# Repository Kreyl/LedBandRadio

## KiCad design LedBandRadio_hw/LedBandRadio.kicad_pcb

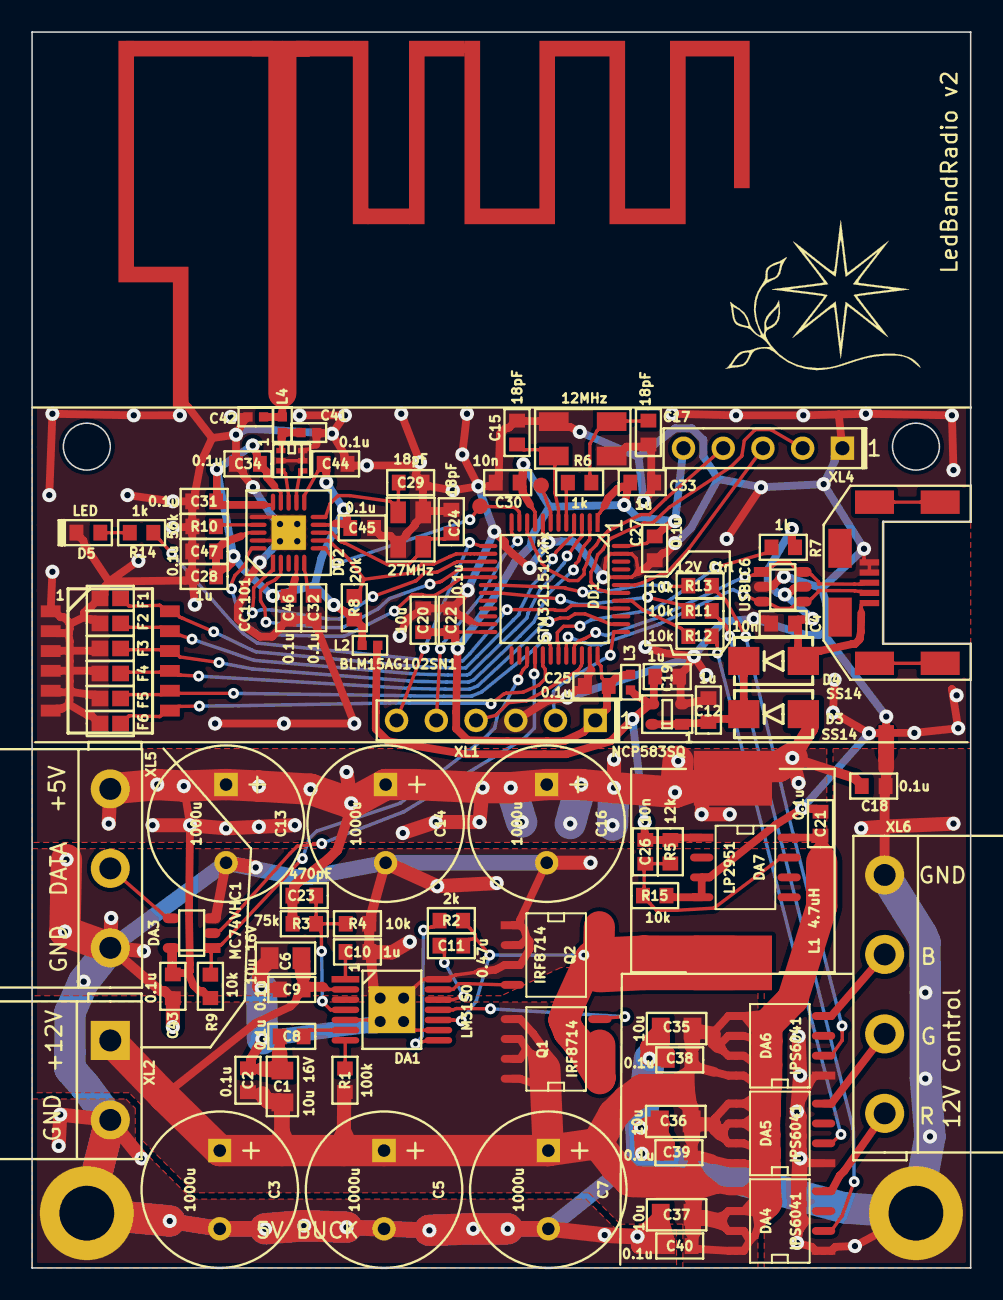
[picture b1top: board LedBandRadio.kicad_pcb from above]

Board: 2 copper layers, 60.0 x 79.0 mm, 104 parts (0 on the bottom side), 66 nets.

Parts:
ANT1: ANT_GENERAL; ANT_INVF_LEDBANDRXTX
BLN1: BALUN868JOHANSON; BALUN_JOHANSON868
C1, C6: 10u 16V; CAP_0805
C2, C8, C9, C18, C21, C22, C25, C27, C31, C32, C34, C38, C39, C40, C43, C44, C45, C46, C47: 0.1u; CAP_0603
C3, C5, C7, C13, C14, C16: 1000u; CAP_10xxR
C4, C26, C30: 10n; CAP_0603
C10, C12, C19, C28, C33: 1u; CAP_0603
C11: 0.47u; CAP_0603
C15, C17, C24, C29: 18pF; CAP_0603
C20: 10u; CAP_0603
C23: 470pF; CAP_0603
C35, C36, C37: 10u; CAP_0805
C41, C42: *; CAP_0402
D3, D4: SS14; SMA_DO214AC
D5: LED; LED_0603
DA1: LM3150; HTSSOP14
DA2: NCP583SQ; SC82AB
DA3: MC74VHC1; SOT23-5
DA4, DA5, DA6: IPS6041; SO8_150MIL
DA7: LP2951; SO8_150MIL
DD1: STM32L151CxTx; LQFP48
DD2: CC1101; QFN20
F1, F2, F3, F4, F5, F6: Fuse0R; RES_0603_FUSE
F7: Fuse0R; FuseShorted
HOLE1, HOLE2: HOLE_METALLED; Hole3_5_out6mm
L1: 4.7uH; 13x13
L2, L3: BLM15AG102SN1; IND_0402
L4: *; IND_0402
Logo1: Logo; Ostranna_12d7_10d1
Q1, Q2: IRF8714; SO8_150MIL
R1: 100k; RES_0603
R2: 2k; RES_0603
R3: 75k; RES_0603
R4, R9, R11, R12, R13, R15: 10k; RES_0603
R5: 12k; RES_0603
R6, R7, R14: 1k; RES_0603
R8: 20k; RES_0603
R10: 56k; RES_0603
SW1: DIPx6; DIP_SMD_1D27X6
TP1, TP2: TESTPOINT; TESTPOINT_1MM
U1: USBLC6; SOT23-6
XL1: CONN_6; PLS-6
XL2: CONN_2; TermiBlockHeader_508_x2_R
XL3: USB_Micro_B; USBmicro_MOLEX_WM17142
XL4: CONN_5; PLS-5
XL5: CONN_3; TermiBlockHeader_508_x3_R
XL6: CONN_4; TermiBlockHeader_508_x4_R
XTAL1: 12MHz; 0503x4-4
XTAL2: 27MHz; 03225C4

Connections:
+3.3V: C19.1, C26.1, DA2.3, DA7.1, L2.2, L3.2, R5.1
+5V: C13.1, C14.1, C16.1, C18.2, C23.2, C43.1, D3.A, DA3.5, L1.1, R3.2, R9.1, XL5.1
+BATT: C1.1, C2.2, C3.1, C5.1, C6.1, C7.1, C9.2, C21.1, C35.1, C36.1, C37.1, C38.1, C39.1, C40.1, DA1.2, DA4.5, DA4.6, DA4.7, DA4.8, DA5.5, DA5.6, DA5.7, DA5.8, DA6.5, DA6.6, DA6.7, DA6.8, DA7.8, Q1.5, Q1.6, Q1.7, Q1.8, R1.2, XL2.1
/5VIN: C12.1, D3.C, D4.C, DA2.1, DA2.4
/5V_USB: C4.1, D4.A, R7.2, U1.5, XL3.1
/12V_B: DD1.18, R13.2
/12V_G: DD1.41, R12.2
/12V_R: DD1.19, R11.2
/ANT1: BLN1.1, C41.1, L4.2
/ANT2: ANT1.1, C42.1, L4.1
/CC_CS: DD1.14, DD2.7, R8.1
/CC_GDO0: DD1.11, DD2.6, TP2.1
/CC_MISO: DD1.16, DD2.2
/CC_MOSI: DD1.17, DD2.20
/CC_SCK: DD1.15, DD2.1
/D+: DD1.33, U1.1, U1.6, XL3.3
/D-: DD1.32, U1.3, U1.4, XL3.2
/DS1: DD1.4, F1.2, SW1.12
/DS2: DD1.3, F2.2, SW1.11
/DS3: DD1.2, F3.2, SW1.10
/DS4: DD1.38, F4.2, SW1.9
/DS5: DD1.30, F5.2, SW1.8
/DS6: DD1.29, F6.2, SW1.7
/L1IN: C11.1, DA1.10, L1.2, Q1.1, Q1.2, Q1.3, Q2.5, Q2.6, Q2.7, Q2.8, R2.1
/OUT_12V_B: DA6.4, XL6.3
/OUT_12V_G: DA5.4, XL6.2
/OUT_12V_R: DA4.4, XL6.1
/RF1: BLN1.4, DD2.12
/RF2: BLN1.3, DD2.13
/SWCLK: DD1.37, XL1.2
/SWDIO: DD1.34, XL1.4
/UART_RX: DD1.13, XL1.6
/UART_TX: DD1.12, XL1.5
/WS_CTRL: DA3.2, DD1.28
/WS_OUT_EN: DA3.1, DD1.27, R9.2
GND: ANT1.2, BLN1.2, BLN1.5, BLN1.6, C4.2, C12.2, C15.2, C17.2, C19.2, C20.1, C21.2, C22.2, C24.2, C25.2, C27.2, C28.2, C29.2, C30.2, C31.2, C32.1, C33.2, C34.2, C41.2, C42.2, C44.2, C45.2, C46.2, C47.2, D5.C, DA2.2, DA7.3, DA7.4, DD1.8, DD1.23, DD1.35, DD1.44, DD1.47, DD2.16, DD2.19, DD2.PAD, F1.1, F2.1, F3.1, F4.1, F5.1, F6.1, F7.1, R10.2, R15.2, SW1.1, SW1.2, SW1.3, SW1.4, SW1.5, SW1.6, U1.2, XL1.3, XL3.4, XL3.5, XL4.1, XTAL1.H, XTAL2.H
GNDPWR: C1.2, C2.1, C3.2, C5.2, C6.2, C7.2, C8.2, C9.1, C10.2, C13.2, C14.2, C16.2, C18.1, C35.2, C36.2, C37.2, C38.2, C39.2, C40.2, C43.2, DA1.5, DA1.9, DA1.14, DA1.PAD, DA3.3, DA4.1, DA5.1, DA6.1, F7.2, HOLE1.H, HOLE2.H, Q2.1, Q2.2, Q2.3, R4.1, XL2.2, XL5.3, XL6.4
unnamed: C8.1, DA1.6
unnamed: C10.1, DA1.1
unnamed: C11.2, DA1.12
unnamed: C15.1, DD1.6, XTAL1.1
unnamed: C17.1, R6.1, XTAL1.2
unnamed: C23.1, DA1.4, R3.1, R4.2
unnamed: C24.1, DD2.8, XTAL2.1
unnamed: C26.2, DA7.7, R5.2, R15.1
unnamed: C29.1, DD2.10, XTAL2.2
unnamed: C32.2, DD2.5
unnamed: D5.A, R14.2
unnamed: DA1.7, R1.1
unnamed: DA1.8, R2.2
unnamed: DA1.11, Q1.4
unnamed: DA1.13, Q2.4
unnamed: DA3.4, XL5.2
unnamed: DA4.2, R11.1
unnamed: DA5.2, R12.1
unnamed: DA6.2, R13.1
unnamed: DD1.5, R6.2
unnamed: DD1.7, TP1.1
unnamed: DD1.10, XL4.4
unnamed: DD1.31, R7.1
unnamed: DD1.40, R14.1
unnamed: DD1.42, XL4.2
unnamed: DD1.43, XL4.3
unnamed: DD2.17, R10.1
PwrMCU: C20.2, C22.1, C25.1, C27.1, C30.1, C33.1, DD1.1, DD1.9, DD1.24, DD1.36, DD1.48, L3.1, XL1.1, XL4.5
VCC: C28.1, C31.1, C34.1, C44.1, C45.1, C46.1, C47.1, DD2.4, DD2.9, DD2.11, DD2.14, DD2.15, DD2.18, L2.1, R8.2

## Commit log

2016-05-09 PCB ready for production
2017-07-09 New +5V sch Still with 3-ch 12V LED control
2017-07-10 v2 sent to factory
2017-07-21 + F030 fw. Works, but not usable.
2017-07-21 * L151 + OS 17.6 works
2017-07-22 + CC + SK6812
2017-07-22 Effects partly rewritten to new engine
2017-07-22 Basic effects done, proceeding with fader.
2017-07-23 Gradienter done without randomiser
2017-07-23 Proceeding with radio
2017-07-23 Antenna matched on the desk
2017-07-23 CC Irq does not fire at RX
2017-07-24 Cmd rx ok, but not handled now
2017-07-24 * 10kBit + new percent in main thd
2017-08-10 * Switch to 359 LEDs * Switch to stm32L151CB
2017-08-10 + Percent to fade
2017-08-10 - DEBUG LED + Percent by radio
2017-08-11 + Save to EEPROM
2017-08-30 StarPath release
2017-08-31 Switch to WS2812 + IntelLedEffs
2017-08-31 Radio control done
2017-09-06 + Effect sequence
2017-09-06 + Asta's sequences added
2019-01-30 * sch
2019-01-30 Switching to Atollic in progress
2020-10-14 + CC updated
2020-10-15 attempt to implement flares
2020-10-15 Flares go up
2020-10-15 + red flash
2020-10-16 + BeWhite + Start Flaming
2020-10-16 + Radio not tested
2020-10-16 Radio works ok
2020-10-16 + Glowing green Release
